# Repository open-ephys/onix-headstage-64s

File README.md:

# ONIX Simplified 64-Channel Headstage
Serialized, multifunction headstage for wire electrode or silicon probe recordings.

- 64x electrophysiology channels
- 3x auxiliary analog channels
- Integrated real-time, room-scale 3D-position tracking
- Integrated absolute orientation tracking

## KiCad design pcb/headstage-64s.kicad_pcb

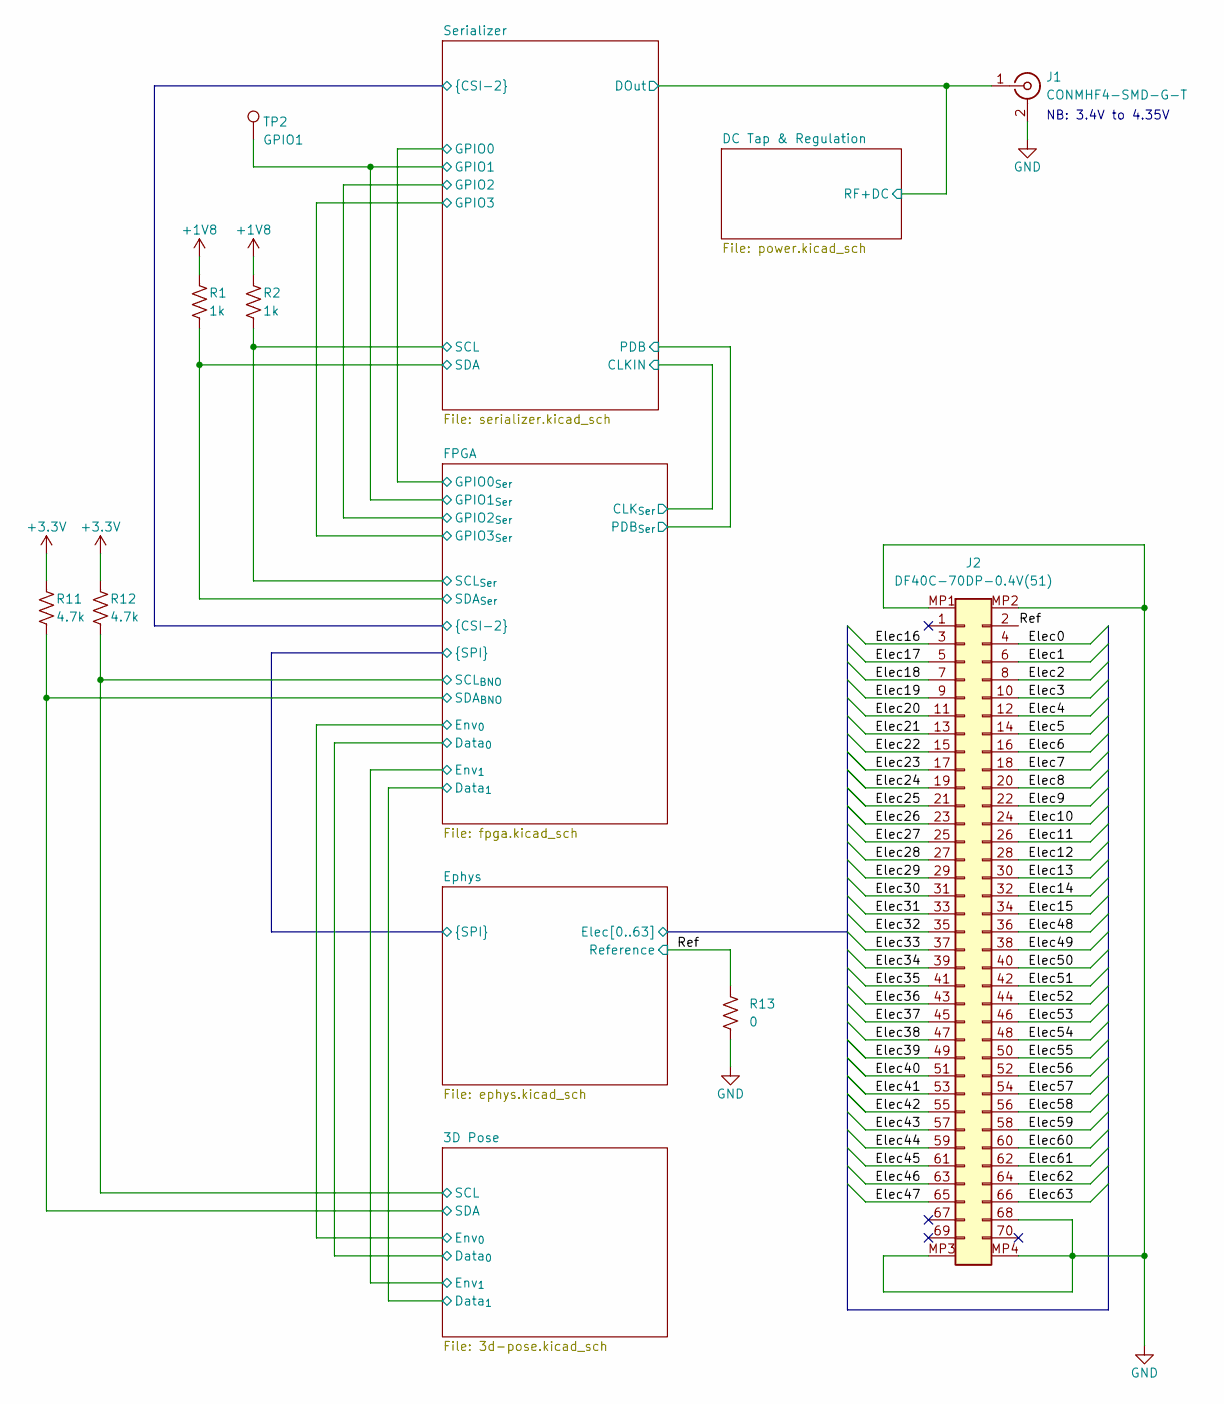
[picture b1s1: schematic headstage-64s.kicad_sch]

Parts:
J1: CONMHF4-SMD-G-T; Coax-Adapter
J2: DF40C-70DP-0.4V(51); HIROSE_DF40C70DP04V51
R1, R2: 1k; R_0201_0603Metric
R11, R12: 4.7k; R_0201_0603Metric
R13: 0; R_0201_0603Metric
TP2: GPIO1; TestPoint_Pad_D0.6mm

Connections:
+1V8: R1.1, R2.1; also elsewhere on the board
+3V3: R11.1, R12.1; also elsewhere on the board
/3D Pose/SCL: R12.2; also elsewhere on the board
/3D Pose/SDA: R11.2; also elsewhere on the board
/DC Tap & Regulation/RF+DC: J1.1 (In); also elsewhere on the board
/Ephys/Elec0: J2.4; also elsewhere on the board
/Ephys/Elec1: J2.6; also elsewhere on the board
/Ephys/Elec2: J2.8; also elsewhere on the board
/Ephys/Elec3: J2.10; also elsewhere on the board
/Ephys/Elec4: J2.12; also elsewhere on the board
/Ephys/Elec5: J2.14; also elsewhere on the board
/Ephys/Elec6: J2.16; also elsewhere on the board
/Ephys/Elec7: J2.18; also elsewhere on the board
/Ephys/Elec8: J2.20; also elsewhere on the board
/Ephys/Elec9: J2.22; also elsewhere on the board
/Ephys/Elec10: J2.24; also elsewhere on the board
/Ephys/Elec11: J2.26; also elsewhere on the board
/Ephys/Elec12: J2.28; also elsewhere on the board
/Ephys/Elec13: J2.30; also elsewhere on the board
/Ephys/Elec14: J2.32; also elsewhere on the board
/Ephys/Elec15: J2.34; also elsewhere on the board
/Ephys/Elec16: J2.3; also elsewhere on the board
/Ephys/Elec17: J2.5; also elsewhere on the board
/Ephys/Elec18: J2.7; also elsewhere on the board
/Ephys/Elec19: J2.9; also elsewhere on the board
/Ephys/Elec20: J2.11; also elsewhere on the board
/Ephys/Elec21: J2.13; also elsewhere on the board
/Ephys/Elec22: J2.15; also elsewhere on the board
/Ephys/Elec23: J2.17; also elsewhere on the board
/Ephys/Elec24: J2.19; also elsewhere on the board
/Ephys/Elec25: J2.21; also elsewhere on the board
/Ephys/Elec26: J2.23; also elsewhere on the board
/Ephys/Elec27: J2.25; also elsewhere on the board
/Ephys/Elec28: J2.27; also elsewhere on the board
/Ephys/Elec29: J2.29; also elsewhere on the board
/Ephys/Elec30: J2.31; also elsewhere on the board
/Ephys/Elec31: J2.33; also elsewhere on the board
/Ephys/Elec32: J2.35; also elsewhere on the board
/Ephys/Elec33: J2.37; also elsewhere on the board
/Ephys/Elec34: J2.39; also elsewhere on the board
/Ephys/Elec35: J2.41; also elsewhere on the board
/Ephys/Elec36: J2.43; also elsewhere on the board
/Ephys/Elec37: J2.45; also elsewhere on the board
/Ephys/Elec38: J2.47; also elsewhere on the board
/Ephys/Elec39: J2.49; also elsewhere on the board
/Ephys/Elec40: J2.51; also elsewhere on the board
/Ephys/Elec41: J2.53; also elsewhere on the board
/Ephys/Elec42: J2.55; also elsewhere on the board
/Ephys/Elec43: J2.57; also elsewhere on the board
/Ephys/Elec44: J2.59; also elsewhere on the board
/Ephys/Elec45: J2.61; also elsewhere on the board
/Ephys/Elec46: J2.63; also elsewhere on the board
/Ephys/Elec47: J2.65; also elsewhere on the board
/Ephys/Elec48: J2.36; also elsewhere on the board
/Ephys/Elec49: J2.38; also elsewhere on the board
/Ephys/Elec50: J2.40; also elsewhere on the board
/Ephys/Elec51: J2.42; also elsewhere on the board
/Ephys/Elec52: J2.44; also elsewhere on the board
/Ephys/Elec53: J2.46; also elsewhere on the board
/Ephys/Elec54: J2.48; also elsewhere on the board
/Ephys/Elec55: J2.50; also elsewhere on the board
/Ephys/Elec56: J2.52; also elsewhere on the board
/Ephys/Elec57: J2.54; also elsewhere on the board
/Ephys/Elec58: J2.56; also elsewhere on the board
/Ephys/Elec59: J2.58; also elsewhere on the board
/Ephys/Elec60: J2.60; also elsewhere on the board
/Ephys/Elec61: J2.62; also elsewhere on the board
/Ephys/Elec62: J2.64; also elsewhere on the board
/Ephys/Elec63: J2.66; also elsewhere on the board
/FPGA/GPIO1_{Ser}: TP2.1; also elsewhere on the board
/FPGA/SCL_{Ser}: R2.2; also elsewhere on the board
/FPGA/SDA_{Ser}: R1.2; also elsewhere on the board
/Ref: J2.2, R13.1; also elsewhere on the board
GND: J1.2 (Ext), J2.68, J2.MP1 (MountPin1), J2.MP2 (MountPin2), J2.MP3 (MountPin3), J2.MP4 (MountPin4), R13.2; also elsewhere on the board

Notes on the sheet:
NB: 3.4V to 4.35V

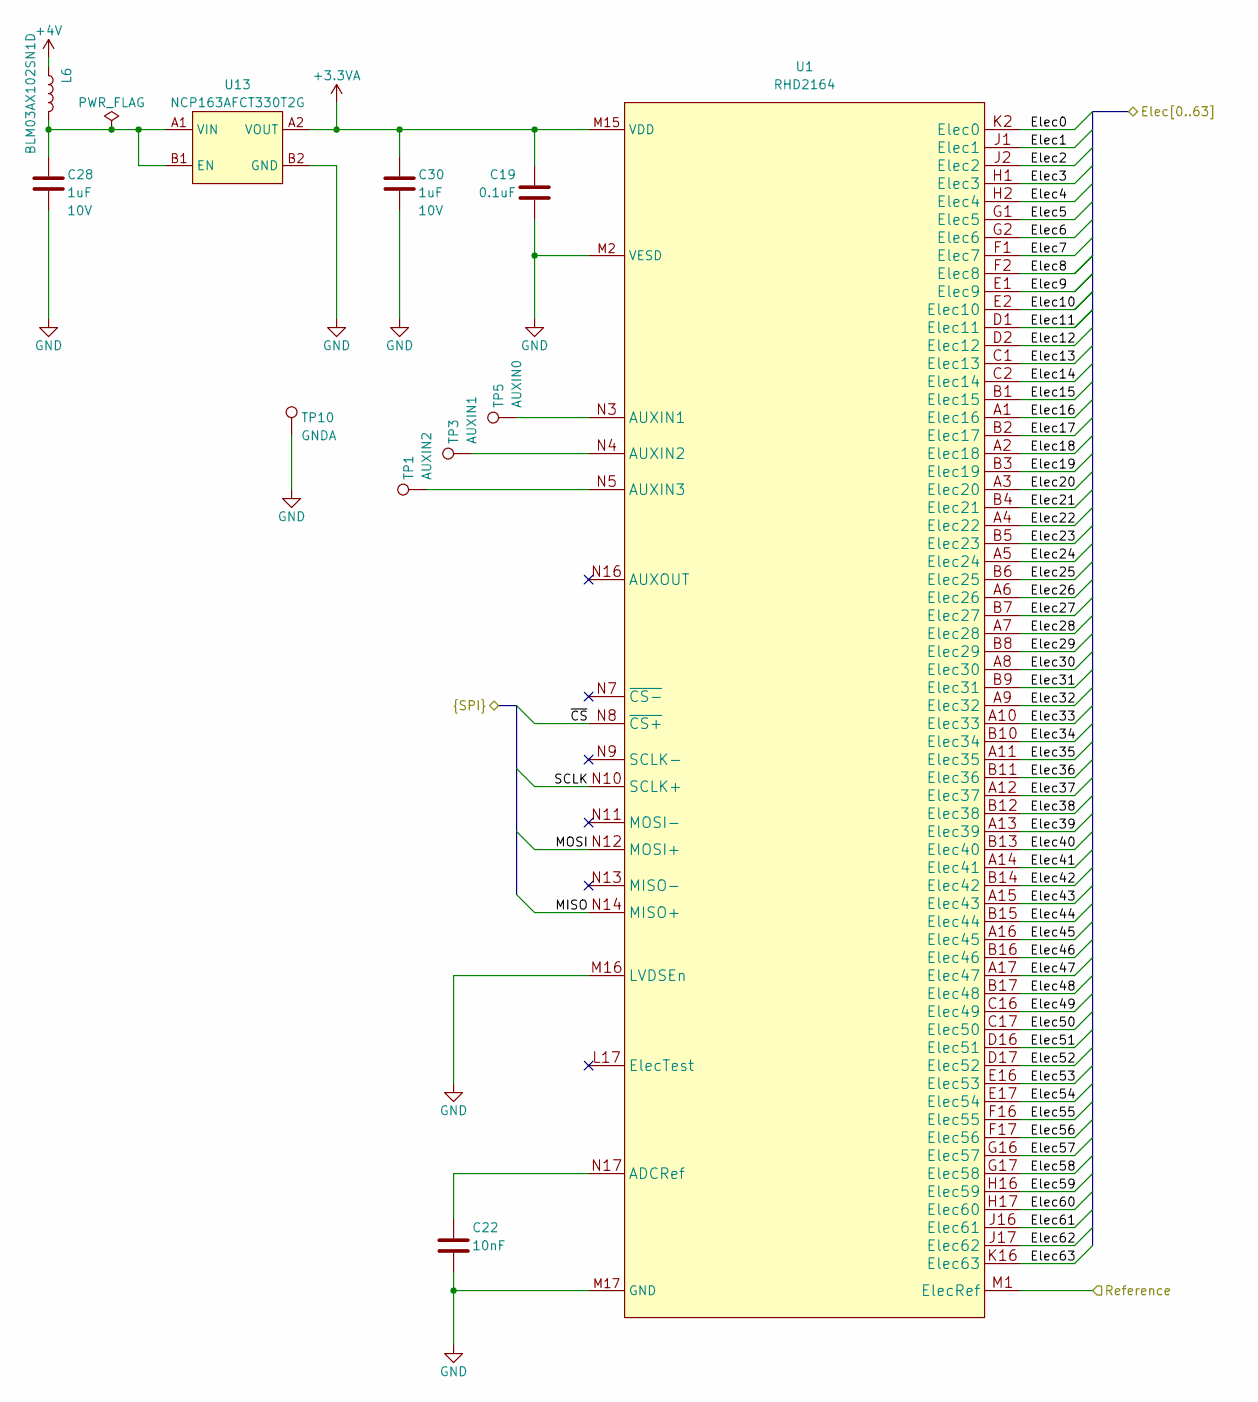
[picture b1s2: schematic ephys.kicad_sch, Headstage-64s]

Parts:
C19: 0.1uF; C_0201_0603Metric; Voltage 16V
C22: 10nF; C_0201_0603Metric; Voltage 35V
C28, C30: 1uF; C_0201_0603Metric; Voltage 10V
L6: BLM03AX102SN1D; L_0201_0603Metric
TP1: AUXIN2; TestPoint_Pad_D0.6mm
TP3: AUXIN1; TestPoint_Pad_D0.6mm
TP5: AUXIN0; TestPoint_Pad_D0.6mm
TP10: GNDA; TestPoint_Pad_D0.6mm
U1: RHD2164; INTAN_BGA-100_17x13_9.0x7.0mm
U13: NCP163AFCT330T2G; ONSEMI_567JZ_WLCSP4-0.64x0.64

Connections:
+3.3VA: C19.1, C30.1, U1.M15 (VDD), U1.N2 (VDD), U1.N15 (VDD), U13.A2 (VOUT)
+4V: L6.1; also elsewhere on the board
/Ephys/Elec0: U1.K2 (Elec0); also elsewhere on the board
/Ephys/Elec1: U1.J1 (Elec1); also elsewhere on the board
/Ephys/Elec2: U1.J2 (Elec2); also elsewhere on the board
/Ephys/Elec3: U1.H1 (Elec3); also elsewhere on the board
/Ephys/Elec4: U1.H2 (Elec4); also elsewhere on the board
/Ephys/Elec5: U1.G1 (Elec5); also elsewhere on the board
/Ephys/Elec6: U1.G2 (Elec6); also elsewhere on the board
/Ephys/Elec7: U1.F1 (Elec7); also elsewhere on the board
/Ephys/Elec8: U1.F2 (Elec8); also elsewhere on the board
/Ephys/Elec9: U1.E1 (Elec9); also elsewhere on the board
/Ephys/Elec10: U1.E2 (Elec10); also elsewhere on the board
/Ephys/Elec11: U1.D1 (Elec11); also elsewhere on the board
/Ephys/Elec12: U1.D2 (Elec12); also elsewhere on the board
/Ephys/Elec13: U1.C1 (Elec13); also elsewhere on the board
/Ephys/Elec14: U1.C2 (Elec14); also elsewhere on the board
/Ephys/Elec15: U1.B1 (Elec15); also elsewhere on the board
/Ephys/Elec16: U1.A1 (Elec16); also elsewhere on the board
/Ephys/Elec17: U1.B2 (Elec17); also elsewhere on the board
/Ephys/Elec18: U1.A2 (Elec18); also elsewhere on the board
/Ephys/Elec19: U1.B3 (Elec19); also elsewhere on the board
/Ephys/Elec20: U1.A3 (Elec20); also elsewhere on the board
/Ephys/Elec21: U1.B4 (Elec21); also elsewhere on the board
/Ephys/Elec22: U1.A4 (Elec22); also elsewhere on the board
/Ephys/Elec23: U1.B5 (Elec23); also elsewhere on the board
/Ephys/Elec24: U1.A5 (Elec24); also elsewhere on the board
/Ephys/Elec25: U1.B6 (Elec25); also elsewhere on the board
/Ephys/Elec26: U1.A6 (Elec26); also elsewhere on the board
/Ephys/Elec27: U1.B7 (Elec27); also elsewhere on the board
/Ephys/Elec28: U1.A7 (Elec28); also elsewhere on the board
/Ephys/Elec29: U1.B8 (Elec29); also elsewhere on the board
/Ephys/Elec30: U1.A8 (Elec30); also elsewhere on the board
/Ephys/Elec31: U1.B9 (Elec31); also elsewhere on the board
/Ephys/Elec32: U1.A9 (Elec32); also elsewhere on the board
/Ephys/Elec33: U1.A10 (Elec33); also elsewhere on the board
/Ephys/Elec34: U1.B10 (Elec34); also elsewhere on the board
/Ephys/Elec35: U1.A11 (Elec35); also elsewhere on the board
/Ephys/Elec36: U1.B11 (Elec36); also elsewhere on the board
/Ephys/Elec37: U1.A12 (Elec37); also elsewhere on the board
/Ephys/Elec38: U1.B12 (Elec38); also elsewhere on the board
/Ephys/Elec39: U1.A13 (Elec39); also elsewhere on the board
/Ephys/Elec40: U1.B13 (Elec40); also elsewhere on the board
/Ephys/Elec41: U1.A14 (Elec41); also elsewhere on the board
/Ephys/Elec42: U1.B14 (Elec42); also elsewhere on the board
/Ephys/Elec43: U1.A15 (Elec43); also elsewhere on the board
/Ephys/Elec44: U1.B15 (Elec44); also elsewhere on the board
/Ephys/Elec45: U1.A16 (Elec45); also elsewhere on the board
/Ephys/Elec46: U1.B16 (Elec46); also elsewhere on the board
/Ephys/Elec47: U1.A17 (Elec47); also elsewhere on the board
/Ephys/Elec48: U1.B17 (Elec48); also elsewhere on the board
/Ephys/Elec49: U1.C16 (Elec49); also elsewhere on the board
/Ephys/Elec50: U1.C17 (Elec50); also elsewhere on the board
/Ephys/Elec51: U1.D16 (Elec51); also elsewhere on the board
/Ephys/Elec52: U1.D17 (Elec52); also elsewhere on the board
/Ephys/Elec53: U1.E16 (Elec53); also elsewhere on the board
/Ephys/Elec54: U1.E17 (Elec54); also elsewhere on the board
/Ephys/Elec55: U1.F16 (Elec55); also elsewhere on the board
/Ephys/Elec56: U1.F17 (Elec56); also elsewhere on the board
/Ephys/Elec57: U1.G16 (Elec57); also elsewhere on the board
/Ephys/Elec58: U1.G17 (Elec58); also elsewhere on the board
/Ephys/Elec59: U1.H16 (Elec59); also elsewhere on the board
/Ephys/Elec60: U1.H17 (Elec60); also elsewhere on the board
/Ephys/Elec61: U1.J16 (Elec61); also elsewhere on the board
/Ephys/Elec62: U1.J17 (Elec62); also elsewhere on the board
/Ephys/Elec63: U1.K16 (Elec63); also elsewhere on the board
/Ephys/MISO: U1.N14 (MISO+); also elsewhere on the board
/Ephys/MOSI: U1.N12 (MOSI+); also elsewhere on the board
/Ephys/SCLK: U1.N10 (SCLK+); also elsewhere on the board
/Ephys/~CS: U1.N8 (~CS+); also elsewhere on the board
/Ref: U1.M1 (ElecRef); also elsewhere on the board
GND: C19.2, C22.2, C28.2, C30.2, TP10.1, U1.M2 (VESD), U1.M16 (LVDSEn), U1.M17 (GND), U1.N1 (GND), U1.N6 (GND), U13.B2 (GND); also elsewhere on the board
unnamed: C22.1, U1.N17 (ADCRef)
unnamed: C28.1, L6.2, U13.A1 (VIN), U13.B1 (EN)
unnamed: TP1.1, U1.N5 (AUXIN3)
unnamed: TP3.1, U1.N4 (AUXIN2)
unnamed: TP5.1, U1.N3 (AUXIN1)

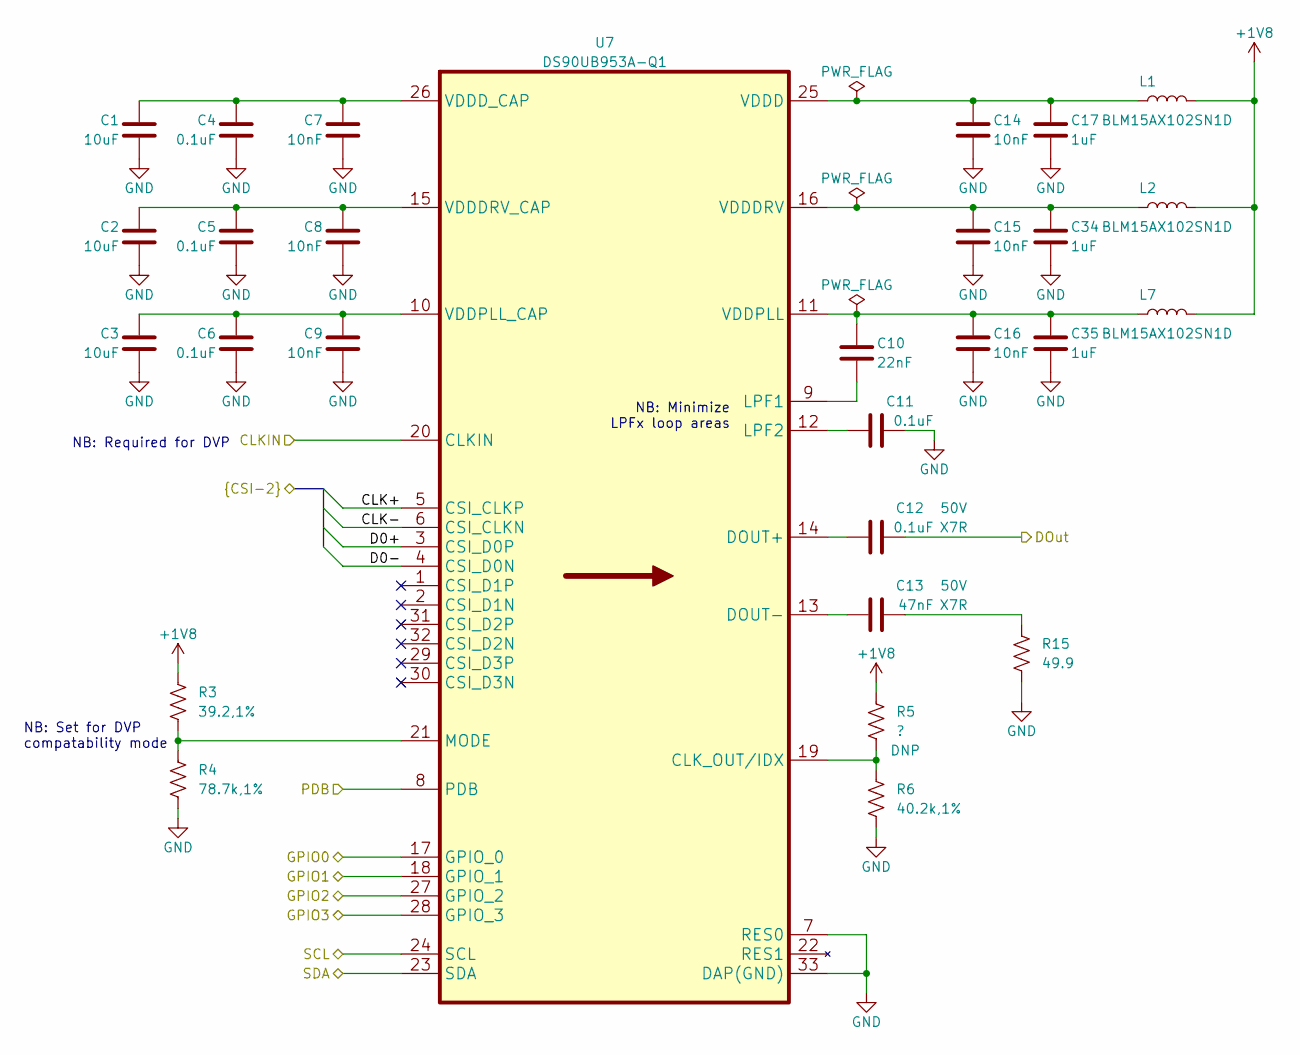
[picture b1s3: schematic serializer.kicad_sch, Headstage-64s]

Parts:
C1, C2, C3: 10uF; C_0402_1005Metric; Voltage 10V
C4, C5, C6, C11: 0.1uF; C_0201_0603Metric; Voltage 16V
C7, C8, C9, C14, C15, C16: 10nF; C_0201_0603Metric; Voltage 35V
C10: 22nF; C_0402_1005Metric; Voltage 35V
C12: 0.1uF; C_0402_1005Metric; Voltage 50V
C13: 47nF; C_0402_1005Metric; Voltage 50V
C17, C34, C35: 1uF; C_0402_1005Metric; Voltage 16V
L1, L2, L7: BLM15AX102SN1D; L_0402_1005Metric
R3: 39.2,1%; R_0201_0603Metric
R4: 78.7k,1%; R_0201_0603Metric
R5: ?; R_0201_0603Metric
R6: 40.2k,1%; R_0201_0603Metric
R15: 49.9; R_0201_0603Metric
U7: DS90UB953A-Q1; TI_RHB0032P

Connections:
+1V8: L1.2, L2.2, L7.2, R3.1, R5.1; also elsewhere on the board
/DC Tap & Regulation/RF+DC: C12.2; also elsewhere on the board
/FPGA/CLK+: U7.5 (CSI_CLKP); also elsewhere on the board
/FPGA/CLK-: U7.6 (CSI_CLKN); also elsewhere on the board
/FPGA/CLK_{Ser}: U7.20 (CLKIN); also elsewhere on the board
/FPGA/D0+: U7.3 (CSI_D0P); also elsewhere on the board
/FPGA/D0-: U7.4 (CSI_D0N); also elsewhere on the board
/FPGA/GPIO0_{Ser}: U7.17 (GPIO_0); also elsewhere on the board
/FPGA/GPIO1_{Ser}: U7.18 (GPIO_1); also elsewhere on the board
/FPGA/GPIO2_{Ser}: U7.27 (GPIO_2); also elsewhere on the board
/FPGA/GPIO3_{Ser}: U7.28 (GPIO_3); also elsewhere on the board
/FPGA/PDB_{Ser}: U7.8 (PDB); also elsewhere on the board
/FPGA/SCL_{Ser}: U7.24 (SCL); also elsewhere on the board
/FPGA/SDA_{Ser}: U7.23 (SDA); also elsewhere on the board
GND: C1.2, C2.2, C3.2, C4.2, C5.2, C6.2, C7.2, C8.2, C9.2, C11.2, C14.2, C15.2, C16.2, C17.2, C34.2, C35.2, R4.2, R6.2, R15.2, U7.7 (RES0), U7.33 (DAP(GND)); also elsewhere on the board
unnamed: C1.1, C4.1, C7.1, U7.26 (VDDD_CAP)
unnamed: C2.1, C5.1, C8.1, U7.15 (VDDDRV_CAP)
unnamed: C3.1, C6.1, C9.1, U7.10 (VDDPLL_CAP)
unnamed: C10.1, C16.1, C35.1, L7.1, U7.11 (VDDPLL)
unnamed: C10.2, U7.9 (LPF1)
unnamed: C11.1, U7.12 (LPF2)
unnamed: C12.1, U7.14 (DOUT+)
unnamed: C13.1, U7.13 (DOUT-)
unnamed: C13.2, R15.1
unnamed: C14.1, C17.1, L1.1, U7.25 (VDDD)
unnamed: C15.1, C34.1, L2.1, U7.16 (VDDDRV)
unnamed: R3.2, R4.1, U7.21 (MODE)
unnamed: R5.2, R6.1, U7.19 (CLK_OUT/IDX)

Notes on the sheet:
NB: Set for DVP compatability mode
NB: Required for DVP
NB: Minimize LPFx loop areas

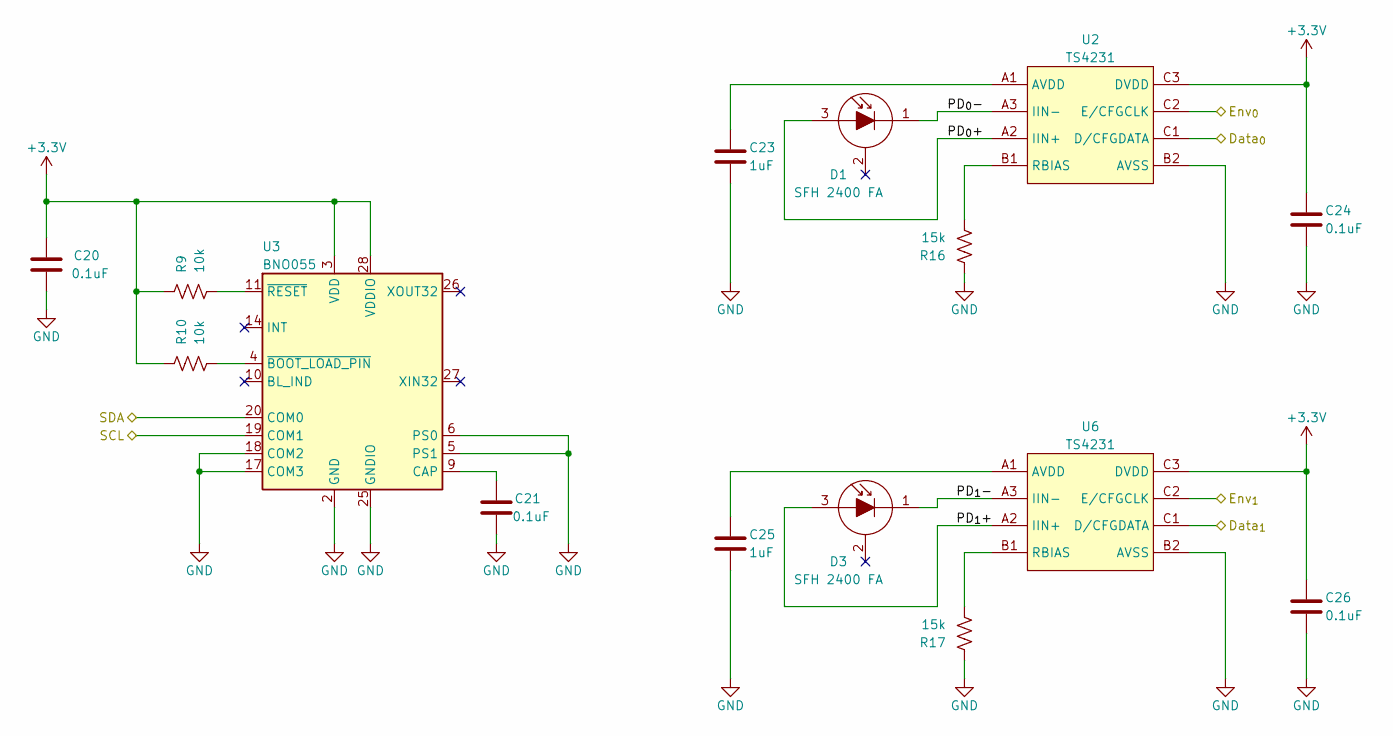
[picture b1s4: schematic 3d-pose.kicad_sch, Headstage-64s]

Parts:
C20, C21, C24, C26: 0.1uF; C_0201_0603Metric; Voltage 16V
C23, C25: 1uF; C_0402_1005Metric; Voltage 16V
D1, D3: SFH 2400 FA; OSRAM_SFH2400FA-Tight
R9, R10: 10k; R_0201_0603Metric
R16, R17: 15k; R_0201_0603Metric
U2, U6: TS4231; TRIAD_BGA-9_3x3_1.7x1.7mm
U3: BNO055; LGA-28_5.2x3.8mm_P0.5mm

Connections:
+3V3: C20.2, C24.2, C26.2, R9.1, R10.1, U2.C3 (DVDD), U3.3 (VDD), U3.28 (VDDIO), U6.C3 (DVDD); also elsewhere on the board
/3D Pose/Data_{0}: U2.C1 (D/CFGDATA); also elsewhere on the board
/3D Pose/Data_{1}: U6.C1 (D/CFGDATA); also elsewhere on the board
/3D Pose/Env_{0}: U2.C2 (E/CFGCLK); also elsewhere on the board
/3D Pose/Env_{1}: U6.C2 (E/CFGCLK); also elsewhere on the board
/3D Pose/PD_{0}+: D1.3 (A), U2.A2 (IIN+)
/3D Pose/PD_{0}-: D1.1 (K), U2.A3 (IIN-)
/3D Pose/PD_{1}+: D3.3 (A), U6.A2 (IIN+)
/3D Pose/PD_{1}-: D3.1 (K), U6.A3 (IIN-)
/3D Pose/SCL: U3.19 (COM1); also elsewhere on the board
/3D Pose/SDA: U3.20 (COM0); also elsewhere on the board
GND: C20.1, C21.1, C23.2, C24.1, C25.2, C26.1, R16.1, R17.1, U2.B2 (AVSS), U2.B3 (AVSS), U3.2 (GND), U3.5 (PS1), U3.6 (PS0), U3.15 (GNDIO), U3.16 (GNDIO), U3.17 (COM3), U3.18 (COM2), U3.25 (GNDIO), U6.B2 (AVSS), U6.B3 (AVSS); also elsewhere on the board
unnamed: C21.2, U3.9 (CAP)
unnamed: C23.1, U2.A1 (AVDD)
unnamed: C25.1, U6.A1 (AVDD)
unnamed: R9.2, U3.11 (~RESET)
unnamed: R10.2, U3.4 (~BOOT_LOAD_PIN)
unnamed: R16.2, U2.B1 (RBIAS)
unnamed: R17.2, U6.B1 (RBIAS)

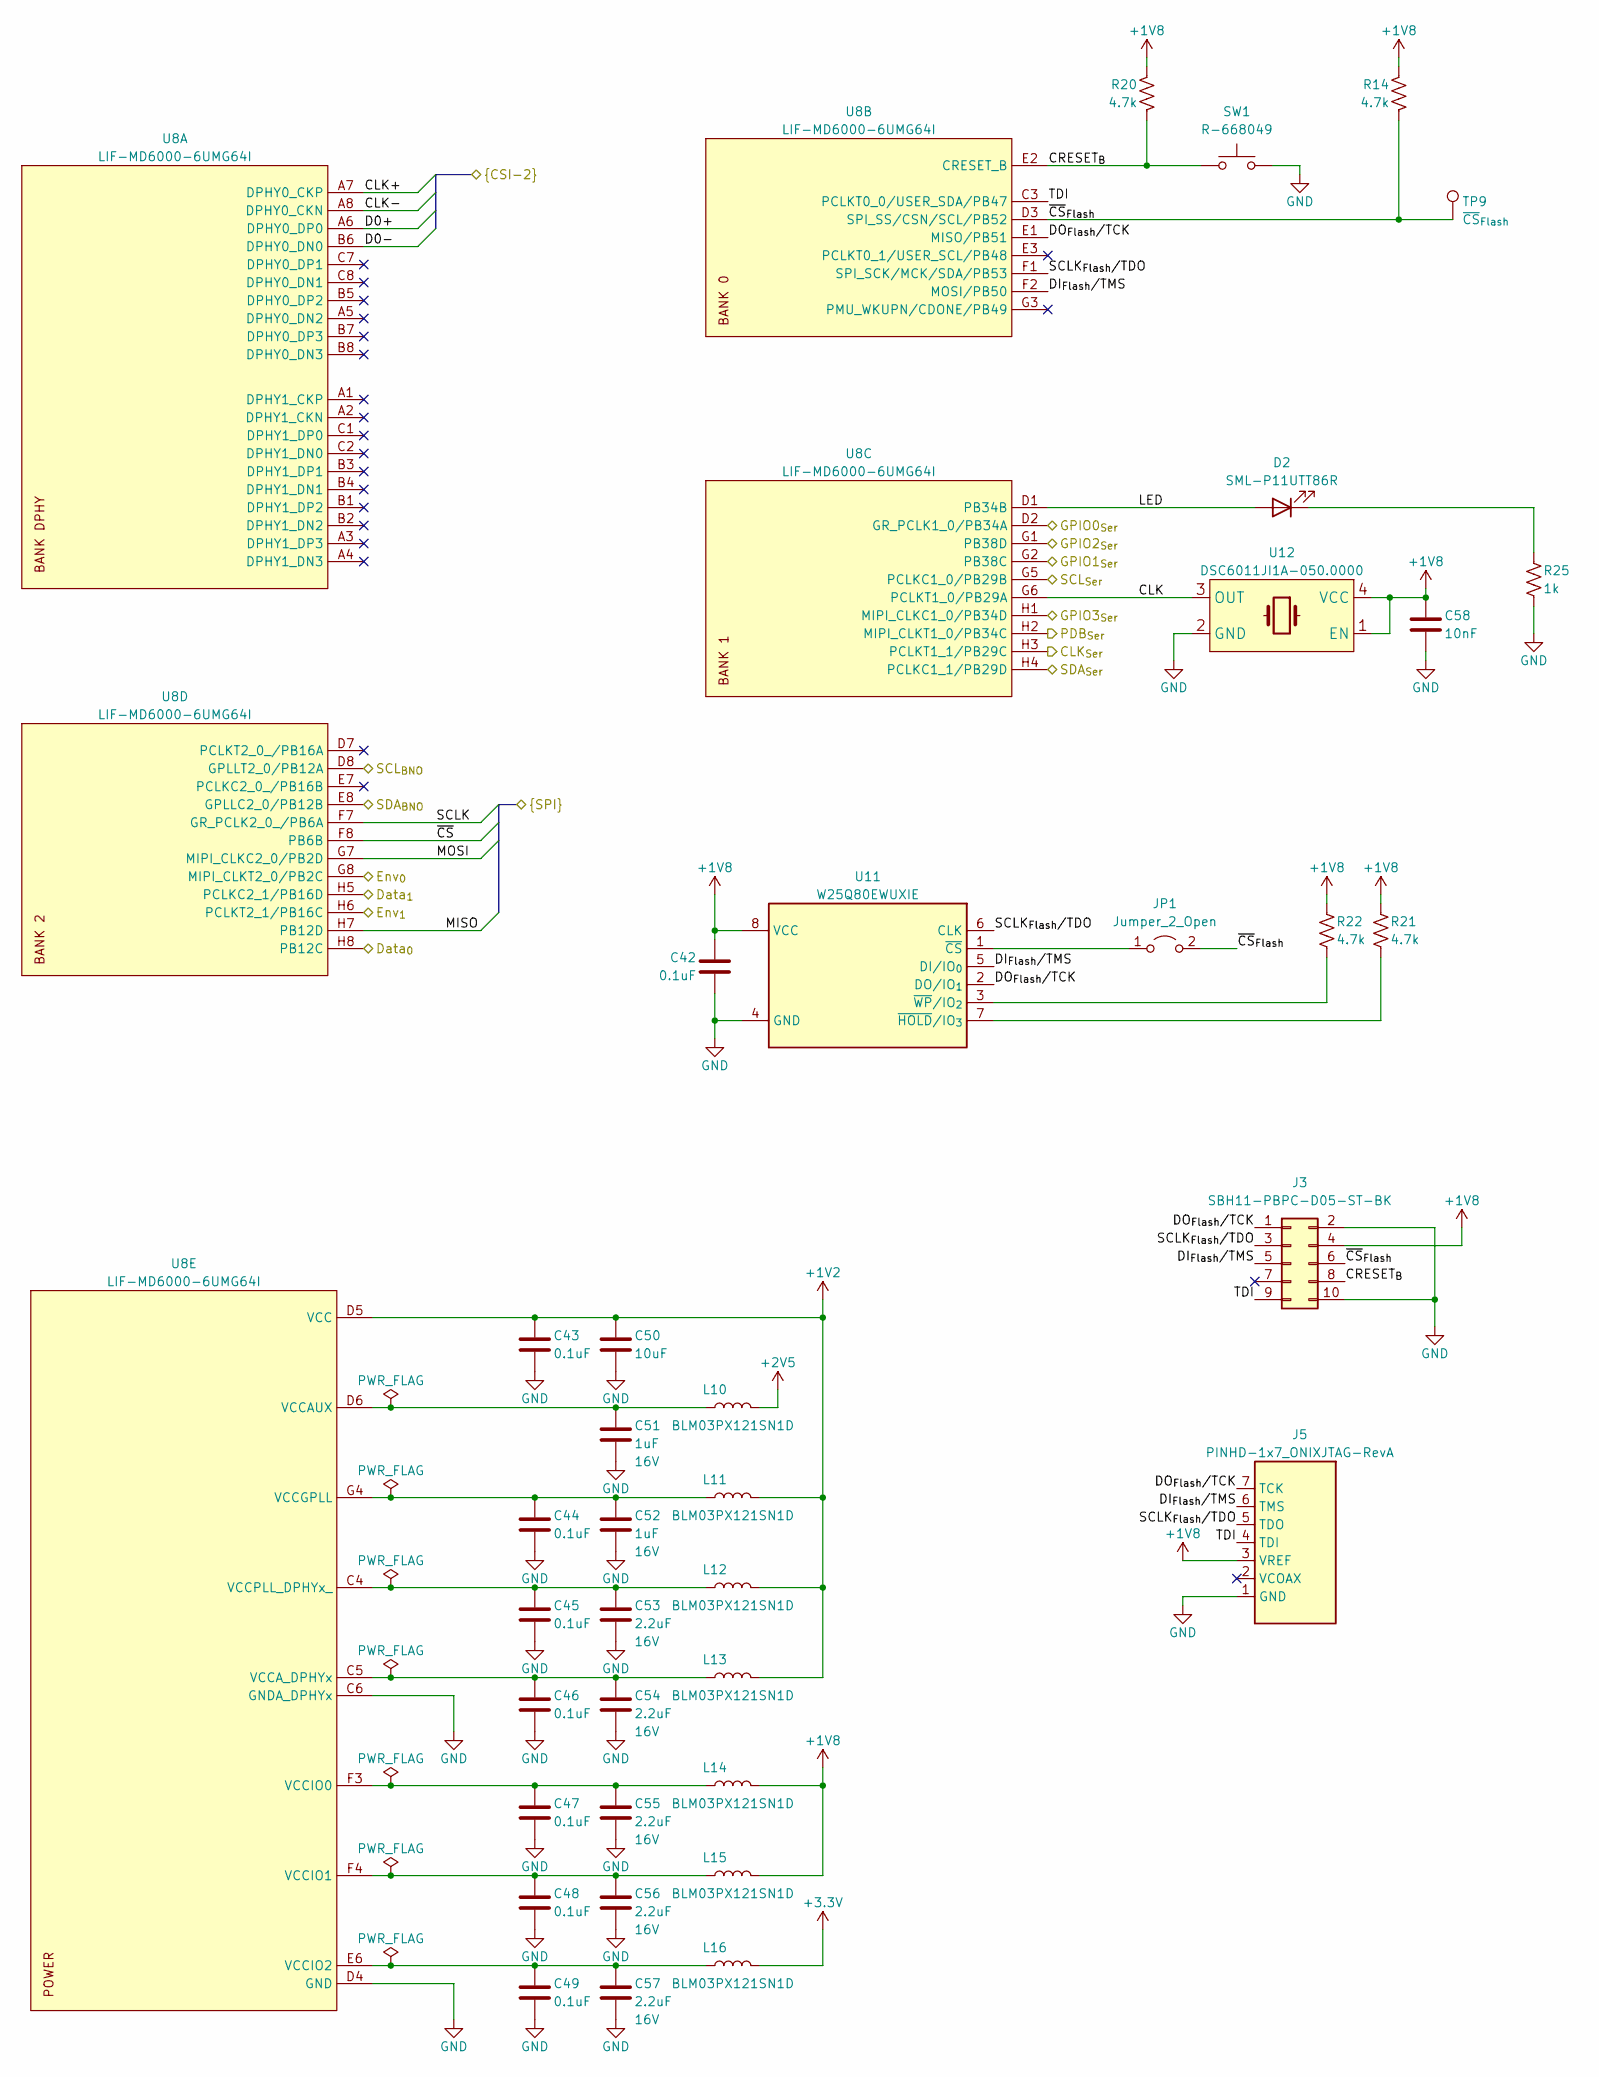
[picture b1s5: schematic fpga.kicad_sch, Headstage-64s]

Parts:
C42, C43, C44, C45, C46, C47, C48, C49: 0.1uF; C_0201_0603Metric; Voltage 16V
C50: 10uF; C_0402_1005Metric; Voltage 10V
C51, C52: 1uF; C_0402_1005Metric; Voltage 16V
C53, C54, C55, C56, C57: 2.2uF; C_0402_1005Metric; Voltage 16V
C58: 10nF; C_0201_0603Metric; Voltage 35V
D2: SML-P11UTT86R; ROHM_SML-P11MTT86R
J3: SBH11-PBPC-D05-ST-BK; IDC-Header_2x05_P2.54mm_Vertical
J5: PINHD-1x7_ONIXJTAG-RevA; ONIXJTAG-RevA
JP1: Jumper_2_Open; OE_SolderJumper-2_0201_Open_Pad
L10, L11, L12, L13, L14, L15, L16: BLM03PX121SN1D; L_0201_0603Metric
R14, R20, R21, R22: 4.7k; R_0201_0603Metric
R25: 1k; R_0201_0603Metric
SW1: R-668049; MITSUMI_R-668049
TP9: ~{CS}_{Flash}; TestPoint_Pad_D0.6mm
U8: LIF-MD6000-6UMG64I; LATTICE_ufcBGA64C40P8X8_3.5X3.5X1.0
U11: W25Q80EWUXIE; WINBOND_USON8-2x3x0.6
U12: DSC6011JI1A-050.0000; MICROCHIP_VFLGA4-2.0x1.6

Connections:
+1V2: C43.1, C50.1, L11.2, L12.2, L13.2, U8.D5 (VCC), U8.E4 (VCC); also elsewhere on the board
+1V8: C42.1, C58.1, J3.4, J5.3 (VREF), L14.2, L15.2, R14.1, R20.1, R21.1, R22.1, U11.8 (VCC), U12.1 (EN), U12.4 (VCC); also elsewhere on the board
+2V5: L10.2; also elsewhere on the board
+3V3: L16.2; also elsewhere on the board
/3D Pose/Data_{0}: U8.H8 (PB12C); also elsewhere on the board
/3D Pose/Data_{1}: U8.H5 (PCLKC2_1/PB16D); also elsewhere on the board
/3D Pose/Env_{0}: U8.G8 (MIPI_CLKT2_0/PB2C); also elsewhere on the board
/3D Pose/Env_{1}: U8.H6 (PCLKT2_1/PB16C); also elsewhere on the board
/3D Pose/SCL: U8.D8 (GPLLT2_0/PB12A); also elsewhere on the board
/3D Pose/SDA: U8.E8 (GPLLC2_0/PB12B); also elsewhere on the board
/Ephys/MISO: U8.H7 (PB12D); also elsewhere on the board
/Ephys/MOSI: U8.G7 (MIPI_CLKC2_0/PB2D); also elsewhere on the board
/Ephys/SCLK: U8.F7 (GR_PCLK2_0_/PB6A); also elsewhere on the board
/Ephys/~CS: U8.F8 (PB6B); also elsewhere on the board
/FPGA/CLK: U8.G6 (PCLKT1_0/PB29A), U12.3 (OUT)
/FPGA/CLK+: U8.A7 (DPHY0_CKP); also elsewhere on the board
/FPGA/CLK-: U8.A8 (DPHY0_CKN); also elsewhere on the board
/FPGA/CLK_{Ser}: U8.H3 (PCLKT1_1/PB29C); also elsewhere on the board
/FPGA/CRESET_{B}: J3.8, R20.2, SW1.1, U8.E2 (CRESET_B)
/FPGA/D0+: U8.A6 (DPHY0_DP0); also elsewhere on the board
/FPGA/D0-: U8.B6 (DPHY0_DN0); also elsewhere on the board
/FPGA/DI_{Flash}/TMS: J3.5, J5.6 (TMS), U8.F2 (MOSI/PB50), U11.5 (DI/IO_{0})
/FPGA/DO_{Flash}/TCK: J3.1, J5.7 (TCK), U8.E1 (MISO/PB51), U11.2 (DO/IO_{1})
/FPGA/GPIO0_{Ser}: U8.D2 (GR_PCLK1_0/PB34A); also elsewhere on the board
/FPGA/GPIO1_{Ser}: U8.G2 (PB38C); also elsewhere on the board
/FPGA/GPIO2_{Ser}: U8.G1 (PB38D); also elsewhere on the board
/FPGA/GPIO3_{Ser}: U8.H1 (MIPI_CLKC1_0/PB34D); also elsewhere on the board
/FPGA/LED: D2.2 (A), U8.D1 (PB34B)
/FPGA/PDB_{Ser}: U8.H2 (MIPI_CLKT1_0/PB34C); also elsewhere on the board
/FPGA/SCLK_{Flash}/TDO: J3.3, J5.5 (TDO), U8.F1 (SPI_SCK/MCK/SDA/PB53), U11.6 (CLK)
/FPGA/SCL_{Ser}: U8.G5 (PCLKC1_0/PB29B); also elsewhere on the board
/FPGA/SDA_{Ser}: U8.H4 (PCLKC1_1/PB29D); also elsewhere on the board
/FPGA/TDI: J3.9, J5.4 (TDI), U8.C3 (PCLKT0_0/USER_SDA/PB47)
/FPGA/~CS_{Flash}: J3.6, JP1.2 (B), R14.2, TP9.1, U8.D3 (SPI_SS/CSN/SCL/PB52)
GND: C42.2, C43.2, C44.2, C45.2, C46.2, C47.2, C48.2, C49.2, C50.2, C51.2, C52.2, C53.2, C54.2, C55.2, C56.2, C57.2, C58.2, J3.2, J3.10, J5.1 (GND), R25.2, SW1.2, U8.C6 (GNDA_DPHYx), U8.D4 (GND), U8.E5 (GND), U8.F5 (GND), U11.4 (GND), U11.9 (GND), U12.2 (GND); also elsewhere on the board
unnamed: C44.1, C52.1, L11.1, U8.G4 (VCCGPLL)
unnamed: C45.1, C53.1, L12.1, U8.C4 (VCCPLL_DPHYx_)
unnamed: C46.1, C54.1, L13.1, U8.C5 (VCCA_DPHYx)
unnamed: C47.1, C55.1, L14.1, U8.F3 (VCCIO0)
unnamed: C48.1, C56.1, L15.1, U8.F4 (VCCIO1)
unnamed: C49.1, C57.1, L16.1, U8.E6 (VCCIO2), U8.F6 (VCCIO2)
unnamed: C51.1, L10.1, U8.D6 (VCCAUX)
unnamed: D2.1 (K), R25.1
unnamed: JP1.1 (A), U11.1 (~CS)
unnamed: R21.2, U11.7 (~HOLD/IO_{3})
unnamed: R22.2, U11.3 (~WP/IO_{2})

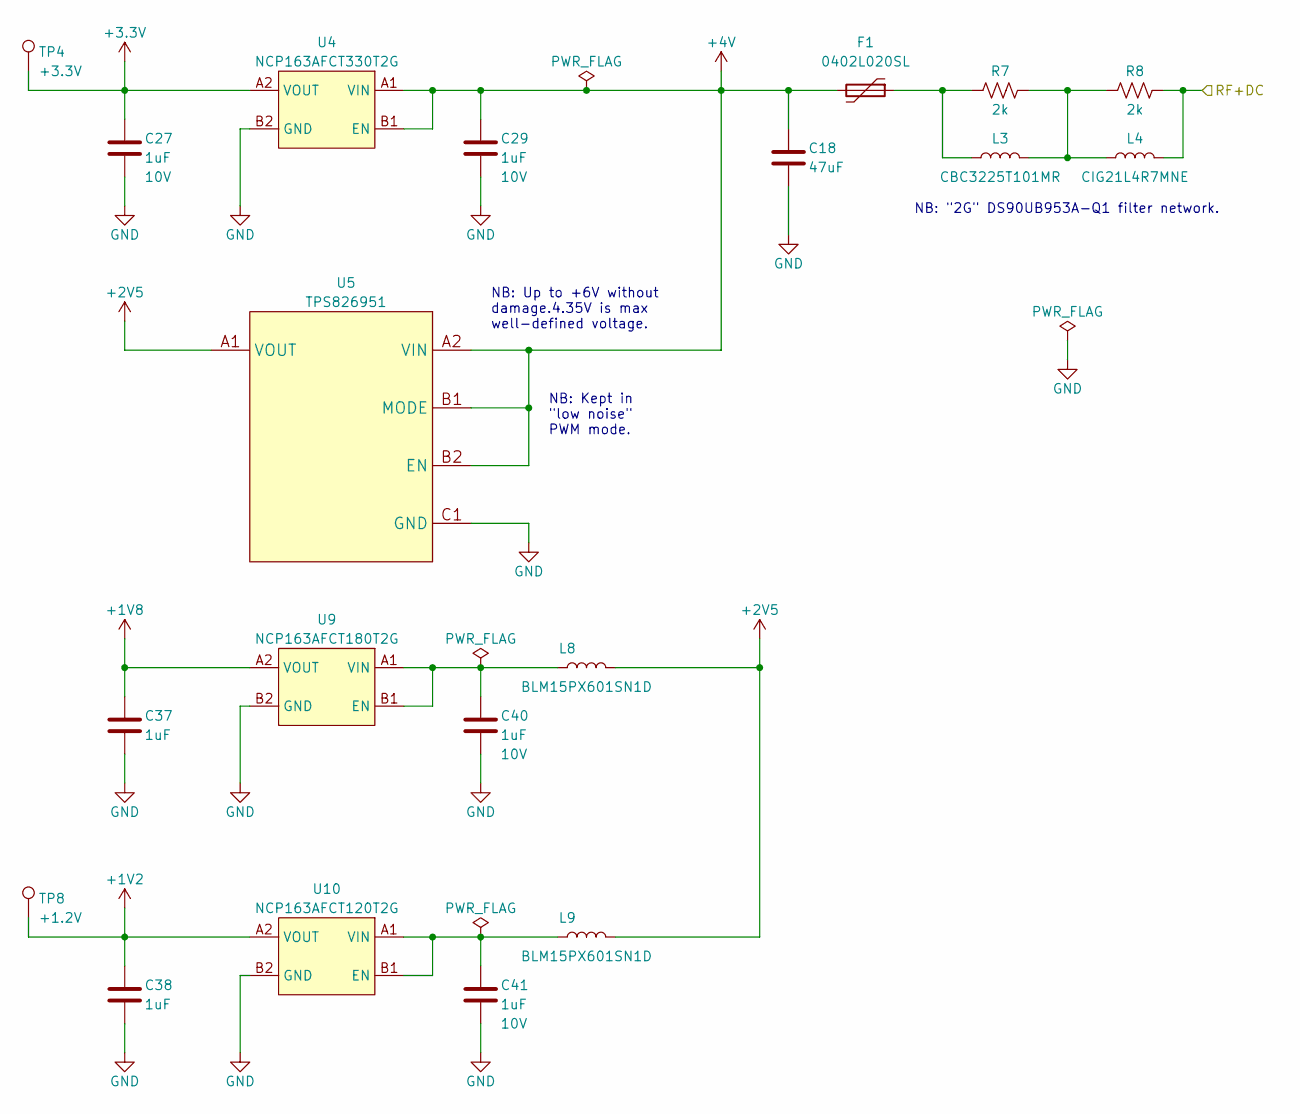
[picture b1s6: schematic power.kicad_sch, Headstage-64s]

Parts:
C18: 47uF; C_0805_2012Metric; Voltage 10V
C27, C29, C37, C38, C40, C41: 1uF; C_0201_0603Metric; Voltage 10V
F1: 0402L020SL; LITTLEFUSE_0402
L3: CBC3225T101MR; L_1210_3225Metric
L4: CIG21L4R7MNE; L_0805_2012Metric
L8, L9: BLM15PX601SN1D; L_0402_1005Metric
R7, R8: 2k; R_0201_0603Metric
TP4: +3.3V; TestPoint_Pad_D0.6mm
TP8: +1.2V; TestPoint_Pad_D0.6mm
U4: NCP163AFCT330T2G; ONSEMI_567JZ_WLCSP4-0.64x0.64
U5: TPS826951; TI_SIP0008B
U9: NCP163AFCT180T2G; ONSEMI_567JZ_WLCSP4-0.64x0.64
U10: NCP163AFCT120T2G; ONSEMI_567JZ_WLCSP4-0.64x0.64

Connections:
+1V2: C38.1, TP8.1, U10.A2 (VOUT); also elsewhere on the board
+1V8: C37.1, U9.A2 (VOUT); also elsewhere on the board
+2V5: L8.2, L9.2, U5.A1 (VOUT); also elsewhere on the board
+3V3: C27.1, TP4.1, U4.A2 (VOUT); also elsewhere on the board
+4V: C18.1, C29.1, F1.2, U4.A1 (VIN), U4.B1 (EN), U5.A2 (VIN), U5.A3 (VIN), U5.B1 (MODE), U5.B2 (EN); also elsewhere on the board
/DC Tap & Regulation/RF+DC: L4.1, R8.2; also elsewhere on the board
GND: C18.2, C27.2, C29.2, C37.2, C38.2, C40.2, C41.2, U4.B2 (GND), U5.C1 (GND), U5.C2 (GND), U5.C3 (GND), U9.B2 (GND), U10.B2 (GND); also elsewhere on the board
unnamed: C40.1, L8.1, U9.A1 (VIN), U9.B1 (EN)
unnamed: C41.1, L9.1, U10.A1 (VIN), U10.B1 (EN)
unnamed: F1.1, L3.1, R7.1
unnamed: L3.2, L4.2, R7.2, R8.1

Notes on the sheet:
NB: Kept in "low noise" PWM mode.
NB: "2G" DS90UB953A-Q1 filter network.
NB: Up to +6V without damage.4.35V is max well-defined voltage.
